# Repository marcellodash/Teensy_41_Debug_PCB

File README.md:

# Teensy_41_Debug_PCB
Teensy 4.1 Debug PCB

Adds support for debugging a Teensy 4.1

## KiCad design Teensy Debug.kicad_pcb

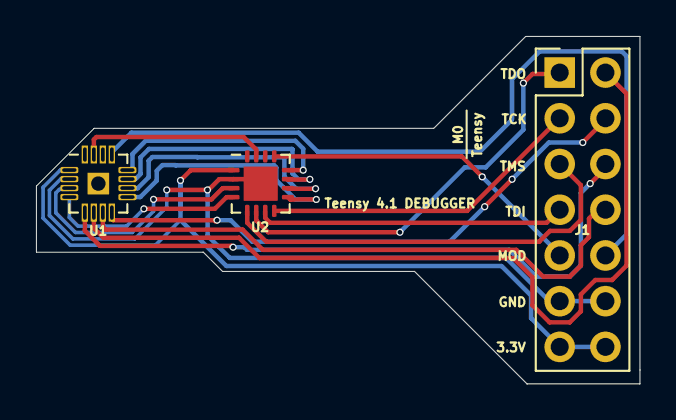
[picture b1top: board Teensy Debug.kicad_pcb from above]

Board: 2 copper layers, 33.5 x 19.3 mm, 3 parts (0 on the bottom side), 19 nets.

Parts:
J1: Conn_02x07_Odd_Even; PinHeader_2x07_P2.54mm_Vertical
U1, U2: MKL02Z32VFG4; QFN-16-1EP_3x3mm_P0.5mm_EP1.9x1.9mm

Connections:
unnamed: J1.1, U2.6
unnamed: J1.2, U1.6
unnamed: J1.3, U2.8
unnamed: J1.4, U1.8
unnamed: J1.5, U2.5
unnamed: J1.6, U1.5
unnamed: J1.7, U2.7
unnamed: J1.8, U1.7
unnamed: J1.9, U2.13
unnamed: J1.10, U1.13
unnamed: J1.11, J1.12, U1.2, U2.2, U2.17
unnamed: J1.13, J1.14, U1.1, U2.1
unnamed: U1.3, U2.3
unnamed: U1.4, U2.4
unnamed: U1.9, U2.9
unnamed: U1.10, U2.10
unnamed: U1.11, U2.11
unnamed: U1.12, U2.12
unnamed: U1.15, U2.15
